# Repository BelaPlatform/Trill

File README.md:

# Trill: Touch Sensing for Makers

Trill sensors are designed to bring beautiful touch interaction to digital projects. Trill sensors are available now on the [Bela Shop](https://shop.bela.io/collections/trill) and via [Mouser Electronics](https://www.mouser.com/c/sensors/sensor-development-tools/?m=Bela).

## Trill libraries and examples

The Bela IDE comes pre-loaded with the [Trill library](https://github.com/BelaPlatform/Bela/tree/master/libraries/Trill) and [Trill examples](https://github.com/BelaPlatform/Bela/tree/master/examples/Trill).

For other platforms:

- [`Trill-Linux`](https://github.com/BelaPlatform/Trill-Linux) contains the Trill library and examples for Linux systems, such as Raspberry Pi

- [`Trill-Arduino`](https://github.com/BelaPlatform/Trill-Arduino) contains the Trill library and examples for Arduino, as well as Arduino-compatible systems such as Teensy. These also include examples of how to connect your Trill sensor to Processing to generate visuals.

## Trill hardware designs

This repo contains the editable PCB designs and manufacturing files for Trill sensors. You can download these schematic source and PCB design files and edit them yourself using [KiCad](https://www.kicad.org/).

### Source Files and Licenses

Trill hardware designs and this datasheet are available under a [Creative Commons Attribution-ShareAlike 4.0 International (CC BY-SA 4.0)](http://creativecommons.org/licenses/by-sa/4.0/) License, meaning they can be freely reused and remixed with attribution, provided modifications remain open source. Trill firmware is licensed under [GNU General Public License 3](https://www.gnu.org/licenses/gpl-3.0.html), meaning that you can freely use, remix, change and extend the code, but you are obligated to make the modified source code available alongside any binaries (flashed, or as files) that you release.

### Commercial Licensing

It's possible to use Trill design files and firmware for a commercial projects free of charge under [CC-BY-SA](http://creativecommons.org/licenses/by-sa/4.0/) (hardware) and [GPL](https://www.gnu.org/licenses/gpl-3.0.en.html) (firmware). Both licenses allow you to use these assets yourself under the license requirements, which include publicly releasing any changes you make to the designs under the same license.

If you want to use Trill design files but not provide attribution and/or not release your source code – for example, because you want to create something to sell using these files but don't want to make your source files public – this is still possible, but requires a commercial license. Augmented Instruments Ltd. can provide you with a commercial license that fits your project and its scope. Get in touch at info@bela.io to discuss your product and the license that's right for you. More information may be found at https://learn.bela.io/products/products-overview/open-source-licenses/#using-trill-in-commercial-products

Please note: The above commercial licensing applies only to modifications to our provided firmware code and PCB designs. You can buy Trill sensors and use them in any commercial or personal project without any additional licensing costs.

## Trill name and logo 

Trill and Bela names and logos are copyright Augmented Instruments Ltd. Any  designs that you release or produce should **not** use the Trill name or logo and/or the Bela name and logo, whether modified or exact copies.

## Datasheet

This repo contains the Trill datasheet. There is one datasheet for all Trill sensors that includes technical diagrams and usage information. 

## Fritzing files

Fritzing parts are available for all Trill sensors, in the [Bela Fritzing repo](https://github.com/belaplatform/fritzing).

## Learn more

The Bela Knowledge Base contains great documentation on using Trill! Visit [learn.bela.io/trill](https://learn.bela.io/trill) for more information, as well as our Get Started Guide.

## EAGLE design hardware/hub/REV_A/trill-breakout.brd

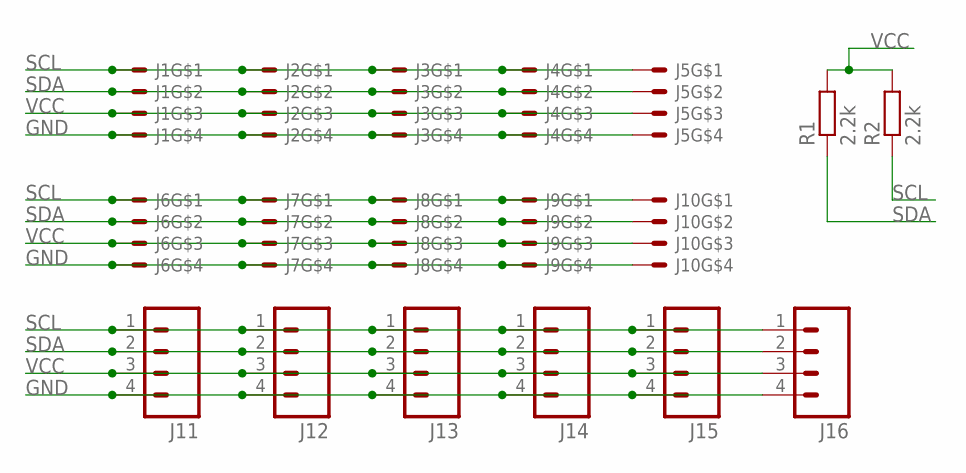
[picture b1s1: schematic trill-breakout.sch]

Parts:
J1, J2, J3, J4, J5, J6, J7, J8, J9, J10: GROVE-SMT; JST-PH-4-SMT
J11, J12, J13, J14, J15, J16: M04LONGPADS; 1X04_LONGPADS
R1, R2: 2.2k; R0603

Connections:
GND: J1.4, J2.4, J3.4, J4.4, J5.4, J6.4, J7.4, J8.4, J9.4, J10.4, J11.4, J12.4, J13.4, J14.4, J15.4, J16.4
SCL: J1.1, J2.1, J3.1, J4.1, J5.1, J6.1, J7.1, J8.1, J9.1, J10.1, J11.1, J12.1, J13.1, J14.1, J15.1, J16.1, R2.1
SDA: J1.2, J2.2, J3.2, J4.2, J5.2, J6.2, J7.2, J8.2, J9.2, J10.2, J11.2, J12.2, J13.2, J14.2, J15.2, J16.2, R1.1
VCC: J1.3, J2.3, J3.3, J4.3, J5.3, J6.3, J7.3, J8.3, J9.3, J10.3, J11.3, J12.3, J13.3, J14.3, J15.3, J16.3, R1.2, R2.2

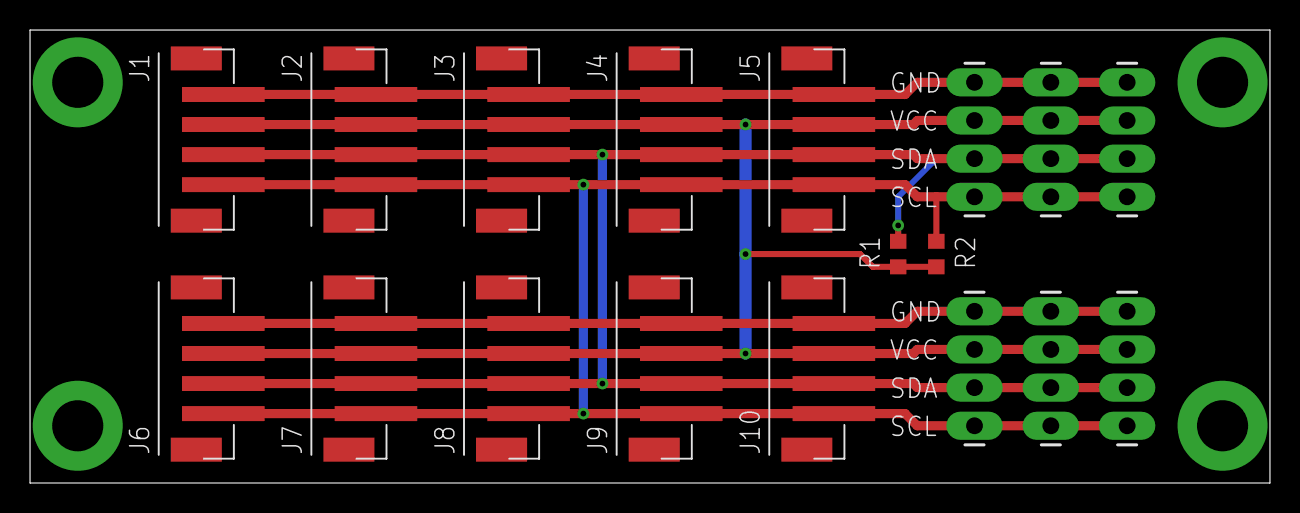
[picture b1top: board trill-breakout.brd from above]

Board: 2 copper layers, 82.5 x 30.1 mm, 18 parts (0 on the bottom side), 4 nets.

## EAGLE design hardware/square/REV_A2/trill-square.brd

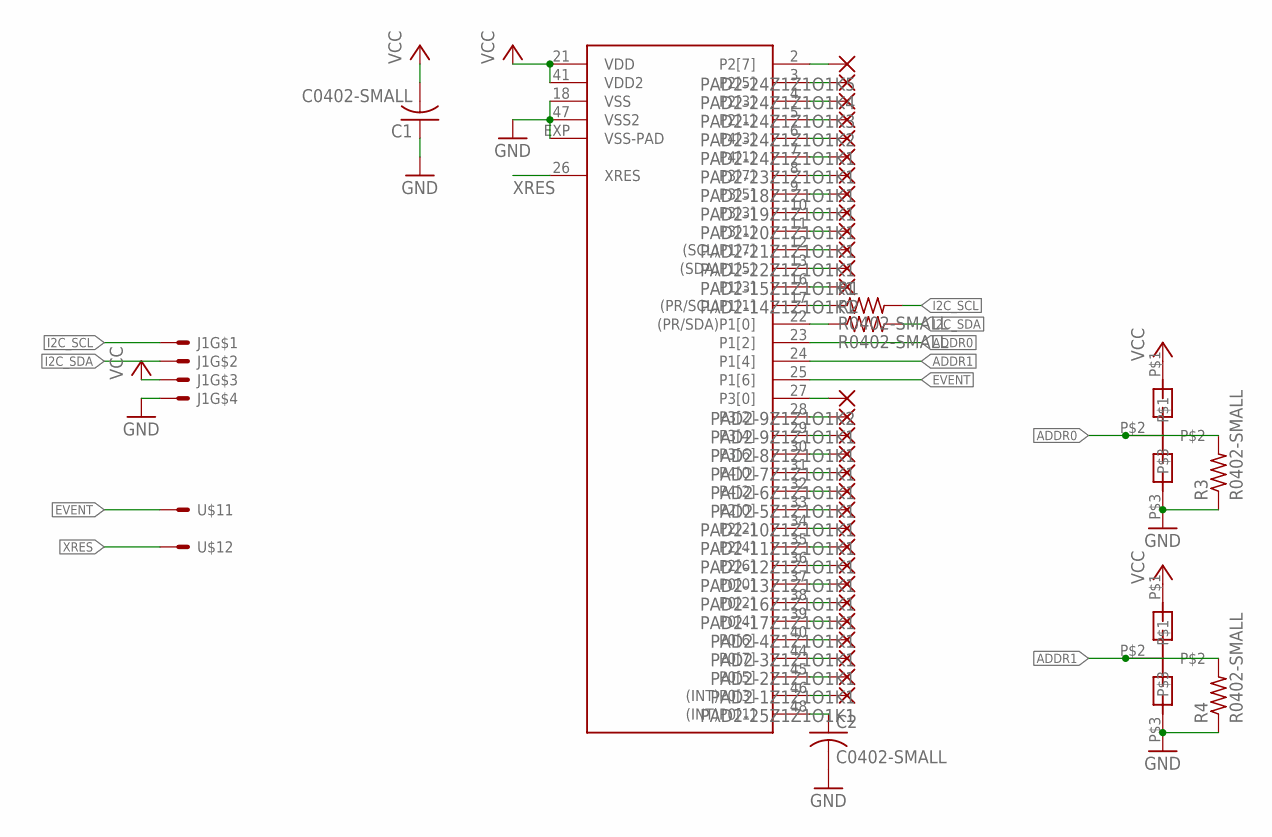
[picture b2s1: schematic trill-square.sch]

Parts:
C1, C2: C0402-SMALL
IC1: CY8C206X6A; QFN48-LEADS
J1: GROVE-SMT; JST-PH-4-SMT
PAD2-1Z1Z1O1K1, PAD2-2Z1Z1O1K1, PAD2-3Z1Z1O1K1, PAD2-4Z1Z1O1K1, PAD2-5Z1Z1O1K1, PAD2-6Z1Z1O1K1, PAD2-7Z1Z1O1K1, PAD2-8Z1Z1O1K1, PAD2-9Z1Z1O1K1, PAD2-9Z1Z1O1K2, PAD2-10Z1Z1O1K1, PAD2-11Z1Z1O1K1, PAD2-12Z1Z1O1K1, PAD2-13Z1Z1O1K1, PAD2-14Z1Z1O1K1, PAD2-15Z1Z1O1K1, PAD2-16Z1Z1O1K1, PAD2-17Z1Z1O1K1, PAD2-18Z1Z1O1K1, PAD2-19Z1Z1O1K1, PAD2-20Z1Z1O1K1, PAD2-21Z1Z1O1K1, PAD2-22Z1Z1O1K1, PAD2-23Z1Z1O1K1, PAD2-24Z1Z1O1K1, PAD2-24Z1Z1O1K2, PAD2-24Z1Z1O1K3, PAD2-24Z1Z1O1K4, PAD2-24Z1Z1O1K5, PAD2-25Z1Z1O1K1: SMD2; SMD1,27-2,54
R1, R2, R3, R4: R0402-SMALL; C0402-SMALL
U$7, U$8: SOLDER_JUMPER_3PAD
U$11, U$12: JST-SMT-EXTRAPAD

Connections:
ADDR0: IC1.23 (P1[2]), R3.P$2 (2), U$7.P$2
ADDR1: IC1.24 (P1[4]), R4.P$2 (2), U$8.P$2
COL1: IC1.27 (P3[0]), PAD2-9Z1Z1O1K2.1
COL2: IC1.28 (P3[2]), PAD2-9Z1Z1O1K1.1
COL3: IC1.29 (P3[4]), PAD2-8Z1Z1O1K1.1
COL4: IC1.30 (P3[6]), PAD2-7Z1Z1O1K1.1
COL5: IC1.31 (P4[0]), PAD2-6Z1Z1O1K1.1
COL6: IC1.32 (P4[2]), PAD2-5Z1Z1O1K1.1
COL7: IC1.33 (P2[0]), PAD2-10Z1Z1O1K1.1
COL8: IC1.13 ((SDA)P1[5]), PAD2-15Z1Z1O1K1.1
COL9: IC1.44 (P0[7]), PAD2-2Z1Z1O1K1.1
COL10: IC1.45 (P0[5]), PAD2-1Z1Z1O1K1.1
COL11: IC1.46 ((INT)P0[3]), PAD2-25Z1Z1O1K1.1
COL12: IC1.3 (P2[5]), PAD2-24Z1Z1O1K4.1
COL13: IC1.4 (P2[3]), PAD2-24Z1Z1O1K3.1
COL14: IC1.5 (P2[1]), PAD2-24Z1Z1O1K2.1
COL15: IC1.6 (P4[3]), PAD2-24Z1Z1O1K1.1
EVENT: IC1.25 (P1[6]), U$11.P$1
GND: C1.P$1 (1), C2.P$2 (2), IC1.18 (VSS), IC1.47 (VSS2), IC1.EXP (VSS-PAD), J1.4, R3.P$1 (1), R4.P$1 (1), U$7.P$3, U$8.P$3
I2C_SCL: J1.1, R1.P$2 (2)
I2C_SDA: J1.2, R2.P$2 (2)
unnamed: C2.P$1 (1), IC1.48 ((INT)P0[1])
unnamed: IC1.17 ((PR/SCL)P1[1]), R1.P$1 (1)
unnamed: IC1.22 ((PR/SDA)P1[0]), R2.P$1 (1)
ROW1: IC1.16 (P1[3]), PAD2-14Z1Z1O1K1.1
ROW2: IC1.12 ((SCL)P1[7]), PAD2-22Z1Z1O1K1.1
ROW3: IC1.11 (P3[1]), PAD2-21Z1Z1O1K1.1
ROW4: IC1.10 (P3[3]), PAD2-20Z1Z1O1K1.1
ROW5: IC1.9 (P3[5]), PAD2-19Z1Z1O1K1.1
ROW6: IC1.8 (P3[7]), PAD2-18Z1Z1O1K1.1
ROW7: IC1.7 (P4[1]), PAD2-23Z1Z1O1K1.1
ROW8: IC1.2 (P2[7]), PAD2-24Z1Z1O1K5.1
ROW9: IC1.34 (P2[2]), PAD2-11Z1Z1O1K1.1
ROW10: IC1.35 (P2[4]), PAD2-12Z1Z1O1K1.1
ROW11: IC1.36 (P2[6]), PAD2-13Z1Z1O1K1.1
ROW12: IC1.37 (P0[0]), PAD2-16Z1Z1O1K1.1
ROW13: IC1.38 (P0[2]), PAD2-17Z1Z1O1K1.1
ROW14: IC1.39 (P0[4]), PAD2-4Z1Z1O1K1.1
ROW15: IC1.40 (P0[6]), PAD2-3Z1Z1O1K1.1
VCC: C1.P$2 (2), IC1.21 (VDD), IC1.41 (VDD2), J1.3, U$7.P$1, U$8.P$1
XRES: IC1.26 (XRES), U$12.P$1

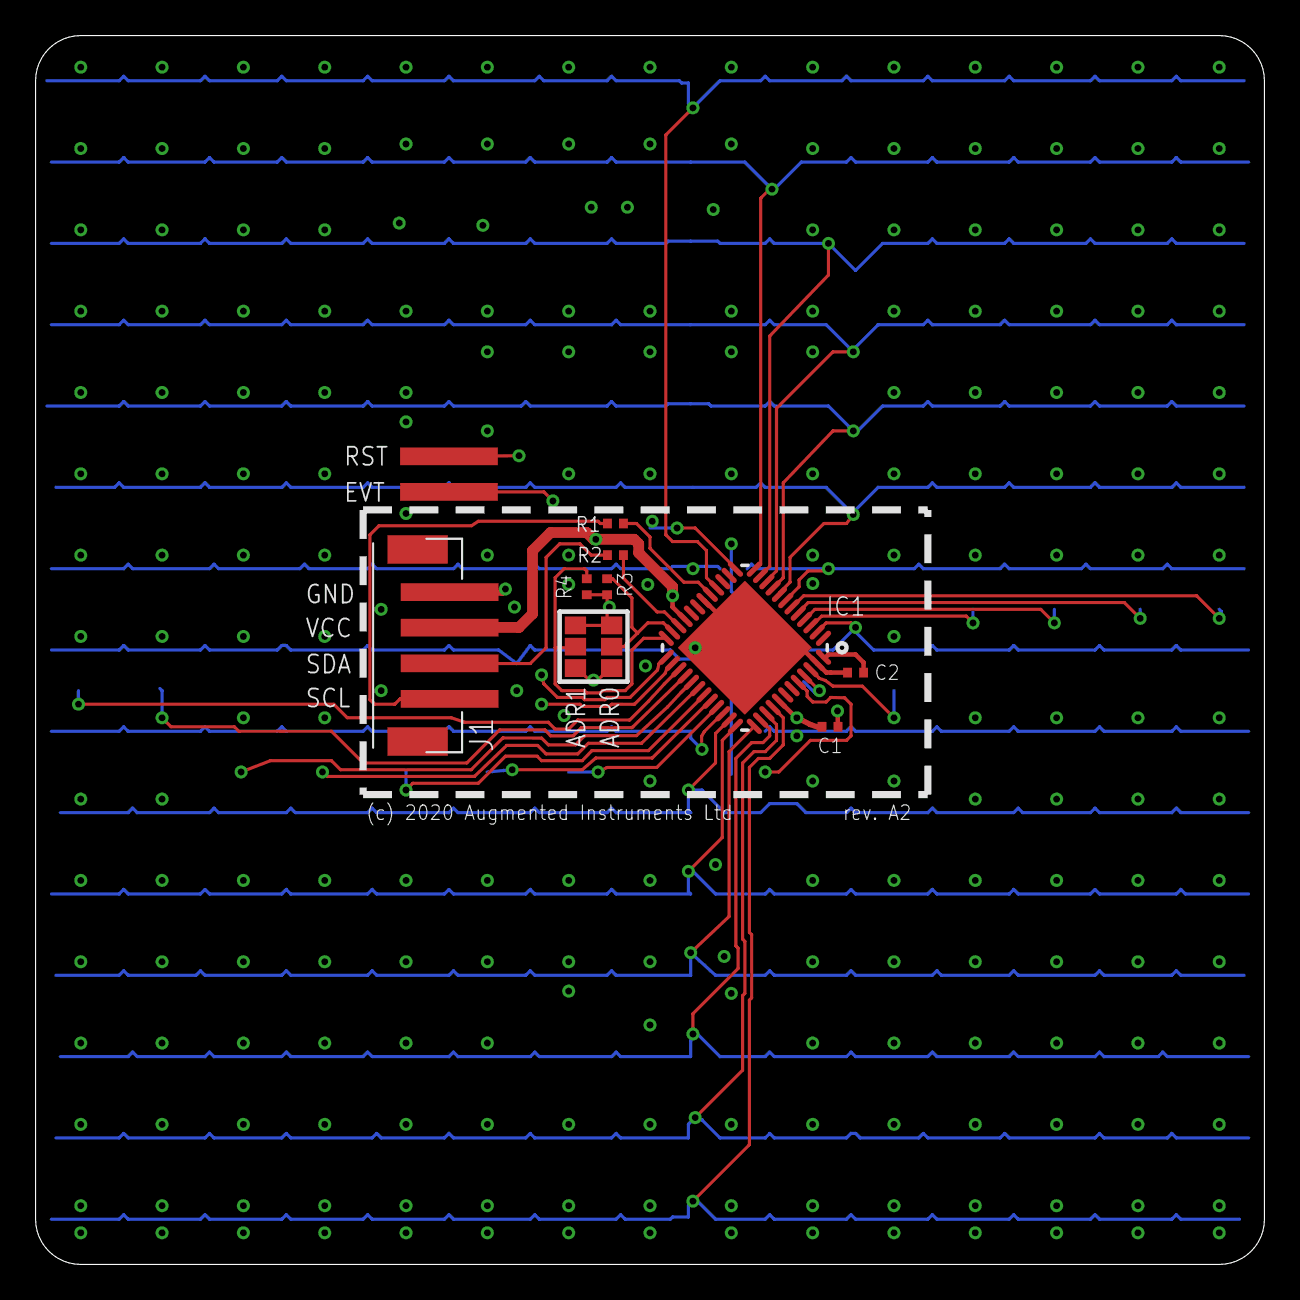
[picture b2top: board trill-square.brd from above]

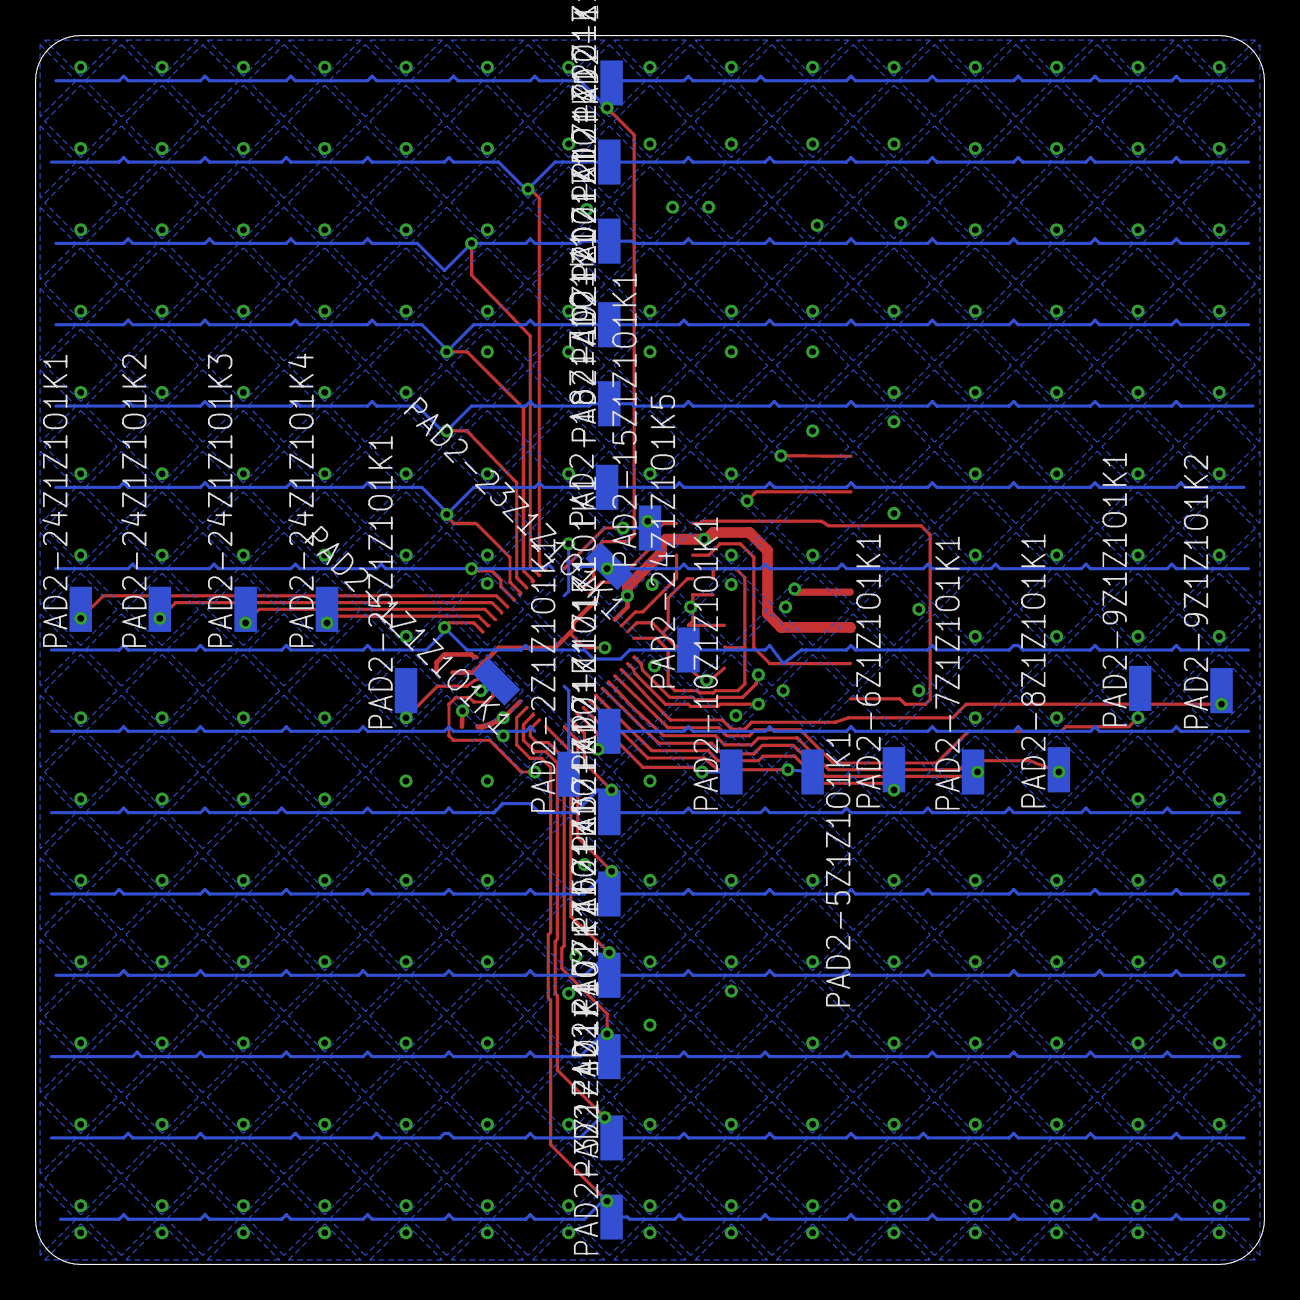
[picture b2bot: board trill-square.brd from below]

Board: 4 copper layers, 69.1 x 69.1 mm, 42 parts (30 on the bottom side), 41 nets.

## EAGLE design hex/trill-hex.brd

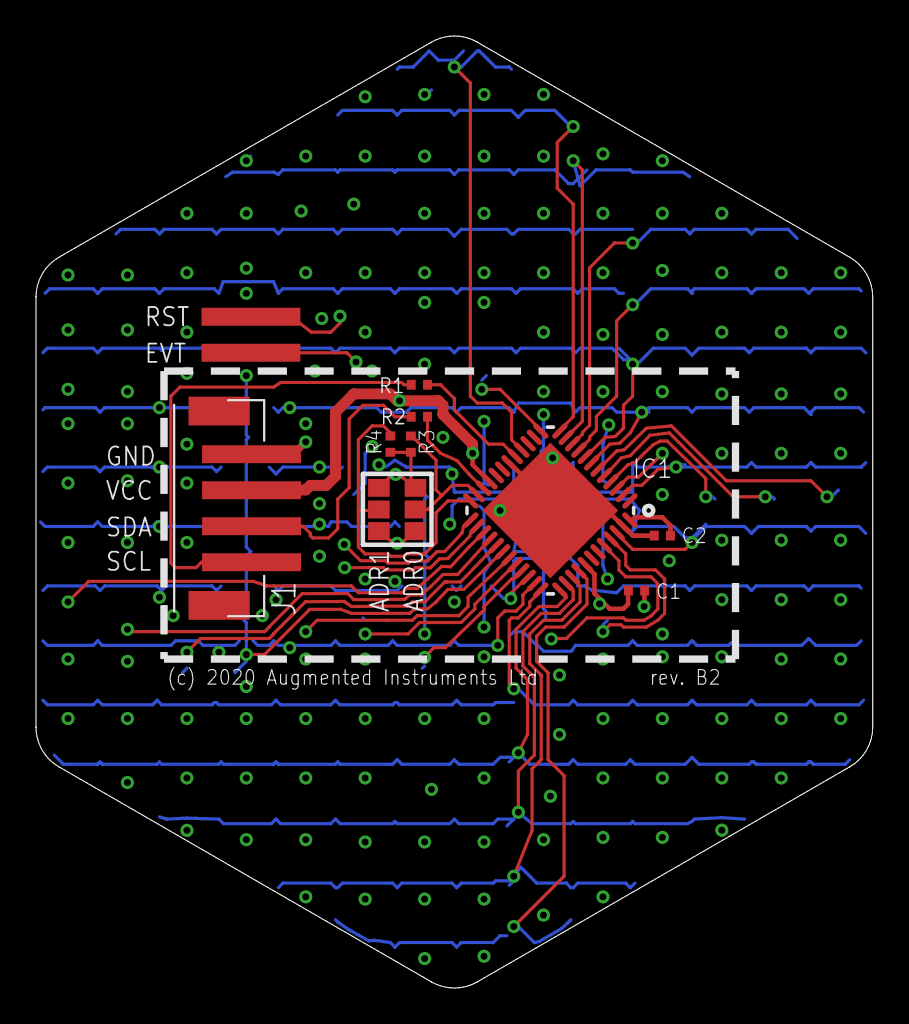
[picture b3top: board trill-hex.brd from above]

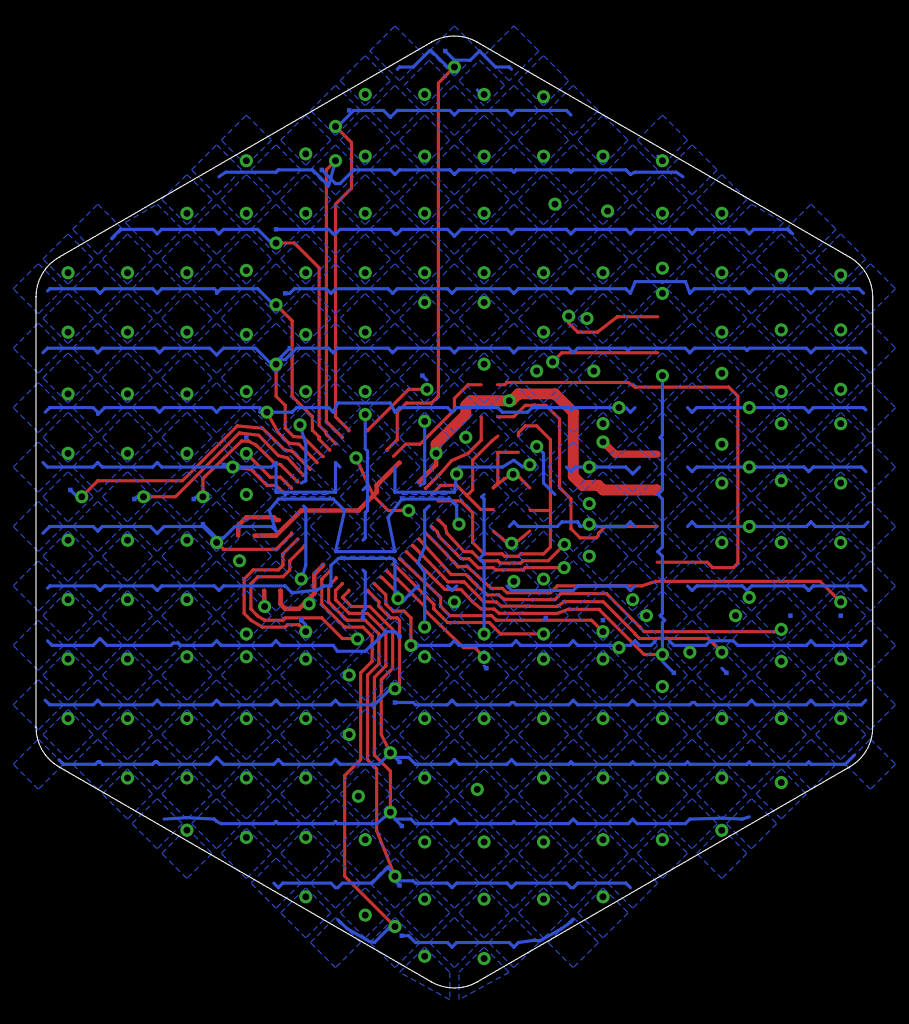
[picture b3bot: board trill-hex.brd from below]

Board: 4 copper layers, 46.5 x 52.9 mm, 42 parts (30 on the bottom side), 41 nets.

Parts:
C1, C2: C0402-SMALL
IC1: CY8C206X6A; QFN48-LEADS
J1: GROVE-SMT; JST-PH-4-SMT
R1, R2, R3, R4: R0402-SMALL; C0402-SMALL
U$1, U$4, U$5, U$6, U$9, U$10, U$13, U$14, U$15, U$16, U$17, U$18, U$19, U$20, U$21, U$22, U$23, U$24, U$25, U$26, U$27, U$28, U$29, U$30, U$31, U$32, U$33, U$34, U$35, U$36: TP-SMALL; TESTPAD-SMALL
U$7, U$8: SOLDER_JUMPER_3PAD
U$11, U$12: JST-SMT-EXTRAPAD

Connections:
ADDR0: IC1.23, R3.P$2, U$7.P$2
ADDR1: IC1.24, R4.P$2, U$8.P$2
COL1: IC1.27, U$4.P$1
COL2: IC1.28, U$5.P$1
COL3: IC1.29, U$1.P$1
COL4: IC1.30, U$6.P$1
COL5: IC1.31, U$9.P$1
COL6: IC1.32, U$10.P$1
COL7: IC1.33, U$13.P$1
COL8: IC1.13, U$35.P$1
COL9: IC1.44, U$21.P$1
COL10: IC1.45, U$22.P$1
COL11: IC1.3, U$25.P$1
COL12: IC1.4, U$26.P$1
COL13: IC1.5, U$27.P$1
COL14: IC1.6, U$28.P$1
EVENT: IC1.25, U$11.P$1
GND: C1.P$1, C2.P$2, IC1.18, IC1.47, IC1.EXP, J1.4, R3.P$1, R4.P$1, U$7.P$3, U$8.P$3
I2C_SCL: J1.1, R1.P$2
I2C_SDA: J1.2, R2.P$2
unnamed: C2.P$1, IC1.48
unnamed: IC1.17, R1.P$1
unnamed: IC1.22, R2.P$1
ROW1: IC1.16, U$36.P$1
ROW2: IC1.12, U$34.P$1
ROW3: IC1.11, U$33.P$1
ROW4: IC1.10, U$32.P$1
ROW5: IC1.9, U$31.P$1
ROW6: IC1.8, U$30.P$1
ROW7: IC1.7, U$29.P$1
ROW8: IC1.2, U$24.P$1
ROW9: IC1.46, U$23.P$1
ROW10: IC1.34, U$14.P$1
ROW11: IC1.35, U$15.P$1
ROW12: IC1.36, U$16.P$1
ROW13: IC1.37, U$17.P$1
ROW14: IC1.38, U$18.P$1
ROW15: IC1.39, U$19.P$1
ROW16: IC1.40, U$20.P$1
VCC: C1.P$2, IC1.21, IC1.41, J1.3, U$7.P$1, U$8.P$1
XRES: IC1.26, U$12.P$1

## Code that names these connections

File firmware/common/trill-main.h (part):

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#define I2C_ADDR_PIN0			(1 << 2)
#define I2C_ADDR_PIN1			(1 << 4)

// Pin for output EVENT signal
#if (ID_DEVICE_TYPE == ID_DEVICE_CRAFT)
#define EVENT_PORT_DATA			PRT2DR
#define EVENT_PORT_DIR0			PRT2DM0
#define EVENT_PORT_DIR1			PRT2DM1
#define EVENT_PIN			(1 << 7)
#else
#define EVENT_PORT_DATA			PRT1DR
#define EVENT_PORT_DIR0			PRT1DM0
#define EVENT_PORT_DIR1			PRT1DM1
#define EVENT_PIN			(1 << 6)
#endif

// Max number of touches to support
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	BYTE address = BASELINE_I2C_ADDRESS;
	BYTE counter;

	// I2C address is determined based on status of ADDR0 and ADDR1 pins
	// which could be in three states: open, tied high, tied low. We first
	// read with a pullup resistor to distinguish between open and tied low;
	// then we read with high-Z to distinguish between open and tied high.
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}

void setEventPin(void) {
	EVENT_PORT_DATA |= EVENT_PIN;
}
void clearEventPin(void) {
	EVENT_PORT_DATA &= ~EVENT_PIN;
}
// for debugging purposes, make it easy to use the address pins as additional
// outputs
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#endif // ID_DEVICE_RING
	WORD posEndOfLoop = (LAST_SENSOR_V - FIRST_SENSOR_V) << SLIDER_BITS;

	// Detect the I2C address from the ADDR0 and ADDR1 pins
	address = detectI2cAddress();

	// Set event pin to strong output (low): DIR1:0 = 01
	EVENT_PORT_DIR1 &= ~EVENT_PIN;
	EVENT_PORT_DIR0 |= EVENT_PIN;
	clearEventPin();

#ifdef ADDRESS_PINS_DEBUG
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				// Copy the two button readings to the end
				wCommBufferInactive[COMM_DATA_OFFSET_WORDS + 2*MAX_NUM_CENTROIDS] = CSD_waSnsDiff[28];
				wCommBufferInactive[COMM_DATA_OFFSET_WORDS + 2*MAX_NUM_CENTROIDS + 1] = CSD_waSnsDiff[29];
				// also set the event pin if any of the "button" pins is active
				bActivityDetected = bActivityDetected || CSD_waSnsDiff[28] || CSD_waSnsDiff[29];
#endif // RING
				break;
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		wCommBufferInactive = wCommBuffers[!bCurrentCommBuffer];
#endif // BUFFER_SWAP

		// If any activity was detected, turn on the event pin, which will
		// be unconditionally cleared elsewhere.
		// An external device monitoring this pin should be looking for a
		// rising edge denoting new data available.
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
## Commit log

2020-06-23 Hardware and datasheet
2020-07-02 Moved hw to subfolder
2020-07-02 Added firmware
2020-11-19 Added BOMs
    Closes https://github.com/BelaPlatform/Trill/issues/2
2021-03-02 Updated datasheet with Trill Flex
2021-03-03 Added Trill Flex files
2021-03-09 fix outline in Edge.cuts layer to be continuous
2022-10-21 KiCad Eagle import or Trill square, gitignore
2023-02-09 Added FLEX to common headers
2023-02-09 Added flex.
    Now on par with Trill_firmware@3d9a512dbde8e439073c2b0662544f1300c713dc
2023-08-03 move datasheet in subfolder
2023-08-03 add REV C datasheet
2023-08-03 renamed REV C datasheet
2023-08-03 update datasheet
2023-08-03 datasheet from 45443b05c4b4d137e50fff726424ba4e64555c03
2023-08-24 Placed REV_C datasheet in place of the old link which is all over the internet
2023-10-19 added current source files for rev C series
2023-10-24 Update README.md
    updated license from CC-BY-SA 3 to 4
2023-10-24 Update README.md
    updated readme to contain same wording and info as the datasheet.
2023-10-24 Update README.md
    removed latex escape character in url
2023-10-24 Update README.md
    let's use mouser.com instead of mouser.it
2023-10-26 added added trill craft as a symbol, footprint and 3dmodel. fixes #5
2023-10-26 relative path to 3dmodel
2023-11-01 updated datasheet to V.1.1
2024-11-08 Datasheet version 1.3
2024-11-08 Updating final v1.3 datasheet
2025-01-31 adding all trill craft footprints
2025-01-31 adding REV3 of Craft design
2025-01-31 Added github action to keep legacy master branch up to date with latest main
2025-02-03 moving remaining craft footprint from general footprint library
2025-02-03 pushing datasheet rev 1.3
2025-02-03 datasheet rev 1.3 in subfolder too

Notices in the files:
firmware/common/trill-main.h:
(c) 2020 Augmented Instruments Ltd
These materials are licensed under the Creative Commons BY-SA-NC 4.0:
Attribution, ShareAlike, Non-Commercial. For further information please
parts and their libraries:
SparkFun-Connectors: Licensing: Creative Commons ShareAlike 4.0 International - https://creativecommons.org/licenses/by-sa/4.0
